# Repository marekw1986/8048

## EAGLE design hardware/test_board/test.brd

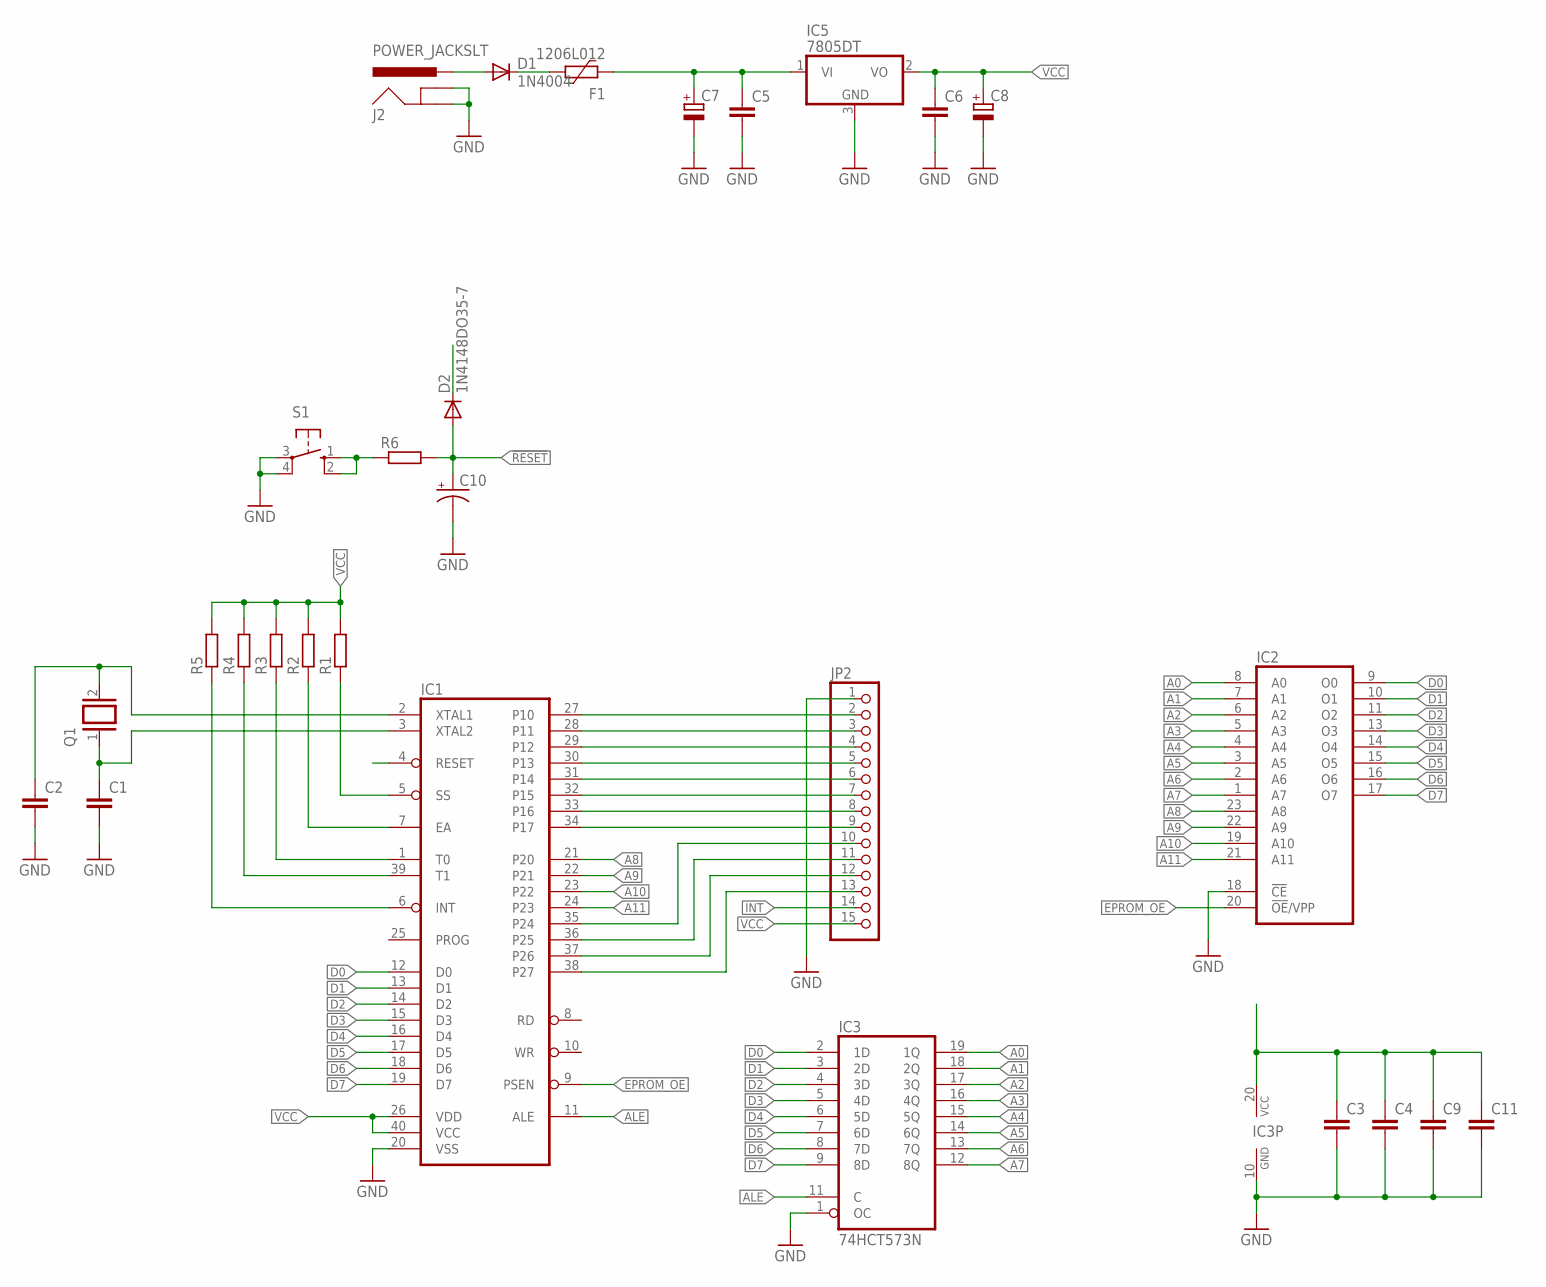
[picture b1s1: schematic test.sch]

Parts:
C1, C2, C3, C4, C5, C6, C9, C11: C-EUC0603; C0603
C7, C8: CPOL-EUSMCB; SMC_B
C10: CPOL-USE2,5-6E; E2,5-6E
D1: 1N4004; DO41-10
D2: 1N4148DO35-7; DO35-7
F1: 1206L012; 1206L
IC1: 8048; DIL40
IC2: 2732; DIL24
IC3: 74HCT573N; DIL20
IC5: 7805DT; TO252
J2: POWER_JACKSLT; POWER_JACK_SLOT
JP2: PINHD-1X15; 1X15
Q1: XTAL/S; QS
R1, R2, R3, R5: R-EU_R1206; R1206
R4, R6: R-EU_R0603; R0603
S1: 10-XX; B3F-10XX

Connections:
9V: C5.1, C7.+, F1.2, IC5.1 (VI)
!RESET: C10.+, D2.A, IC1.4 (RESET), R6.2
A0: IC2.8 (A0), IC3.19 (1Q)
A1: IC2.7 (A1), IC3.18 (2Q)
A2: IC2.6 (A2), IC3.17 (3Q)
A3: IC2.5 (A3), IC3.16 (4Q)
A4: IC2.4 (A4), IC3.15 (5Q)
A5: IC2.3 (A5), IC3.14 (6Q)
A6: IC2.2 (A6), IC3.13 (7Q)
A7: IC2.1 (A7), IC3.12 (8Q)
A8: IC1.21 (P20), IC2.23 (A8)
A9: IC1.22 (P21), IC2.22 (A9)
A10: IC1.23 (P22), IC2.19 (A10)
A11: IC1.24 (P23), IC2.21 (A11)
ALE: IC1.11 (ALE), IC3.11 (C)
D0: IC1.12 (D0), IC2.9 (O0), IC3.2 (1D)
D1: IC1.13 (D1), IC2.10 (O1), IC3.3 (2D)
D2: IC1.14 (D2), IC2.11 (O2), IC3.4 (3D)
D3: IC1.15 (D3), IC2.13 (O3), IC3.5 (4D)
D4: IC1.16 (D4), IC2.14 (O4), IC3.6 (5D)
D5: IC1.17 (D5), IC2.15 (O5), IC3.7 (6D)
D6: IC1.18 (D6), IC2.16 (O6), IC3.8 (7D)
D7: IC1.19 (D7), IC2.17 (O7), IC3.9 (8D)
EPROM_OE: IC1.9 (PSEN), IC2.20 (!OE!/VPP)
GND: C1.2, C2.2, C3.2, C4.2, C5.2, C6.2, C7.-, C8.-, C9.2, C10.-, C11.2, IC1.20 (VSS), IC2.12 (GND), IC2.18 (!CE), IC3.1 (OC), IC3.10 (GND), IC5.3 (GND), J2.GND@1 (GNDBREAK), J2.GND@2 (GND), JP2.1, S1.3, S1.4 (P1)
INT: IC1.6 (INT), JP2.14, R5.1
unnamed: C1.1, IC1.3 (XTAL2), Q1.1
unnamed: C2.1, IC1.2 (XTAL1), Q1.2
unnamed: IC1.5 (SS), R1.1
unnamed: IC1.7 (EA), R2.1
unnamed: IC1.1 (T0), R3.1
unnamed: IC1.39 (T1), R4.1
unnamed: R6.1, S1.1 (S), S1.2 (S1)
unnamed: IC1.27 (P10), JP2.2
unnamed: IC1.28 (P11), JP2.3
unnamed: IC1.29 (P12), JP2.4
unnamed: IC1.30 (P13), JP2.5
unnamed: IC1.31 (P14), JP2.6
unnamed: IC1.32 (P15), JP2.7
unnamed: IC1.33 (P16), JP2.8
unnamed: IC1.34 (P17), JP2.9
unnamed: IC1.35 (P24), JP2.10
unnamed: D1.A, J2.PWR
unnamed: IC1.36 (P25), JP2.11
unnamed: D1.C, F1.1
unnamed: IC1.37 (P26), JP2.12
unnamed: IC1.38 (P27), JP2.13
VCC: C3.1, C4.1, C6.1, C8.+, C9.1, C11.1, D2.C, IC1.26 (VDD), IC1.40 (VCC), IC2.24 (VCC), IC3.20 (VCC), IC5.2 (VO), JP2.15, R1.2, R2.2, R3.2, R4.2, R5.2

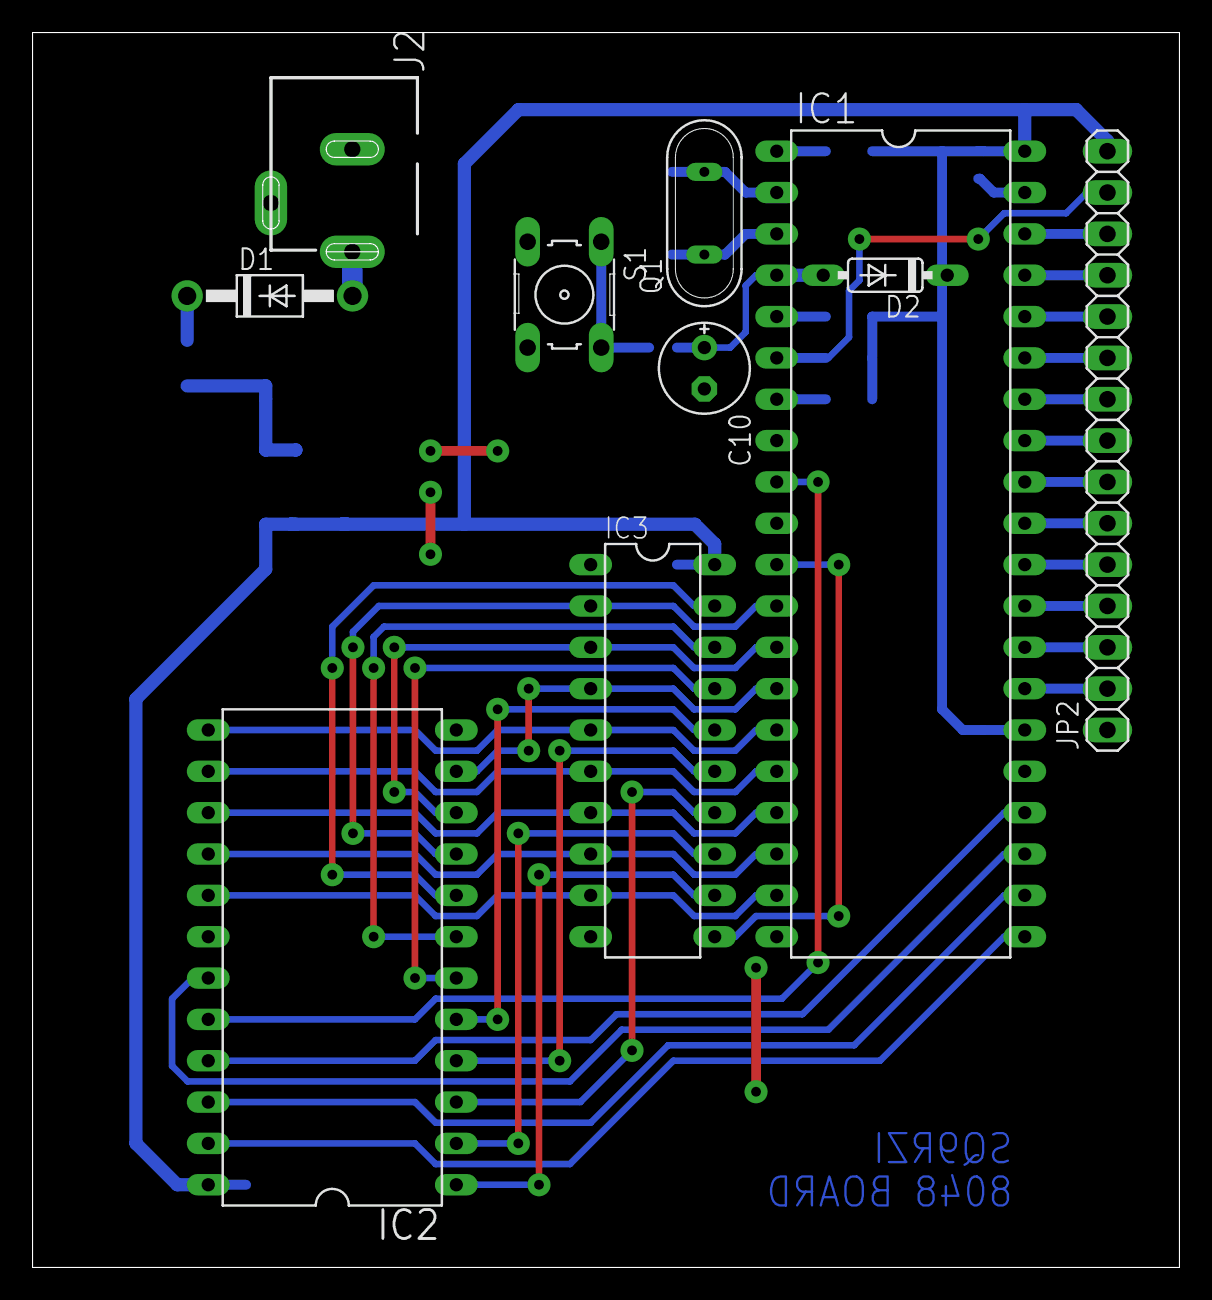
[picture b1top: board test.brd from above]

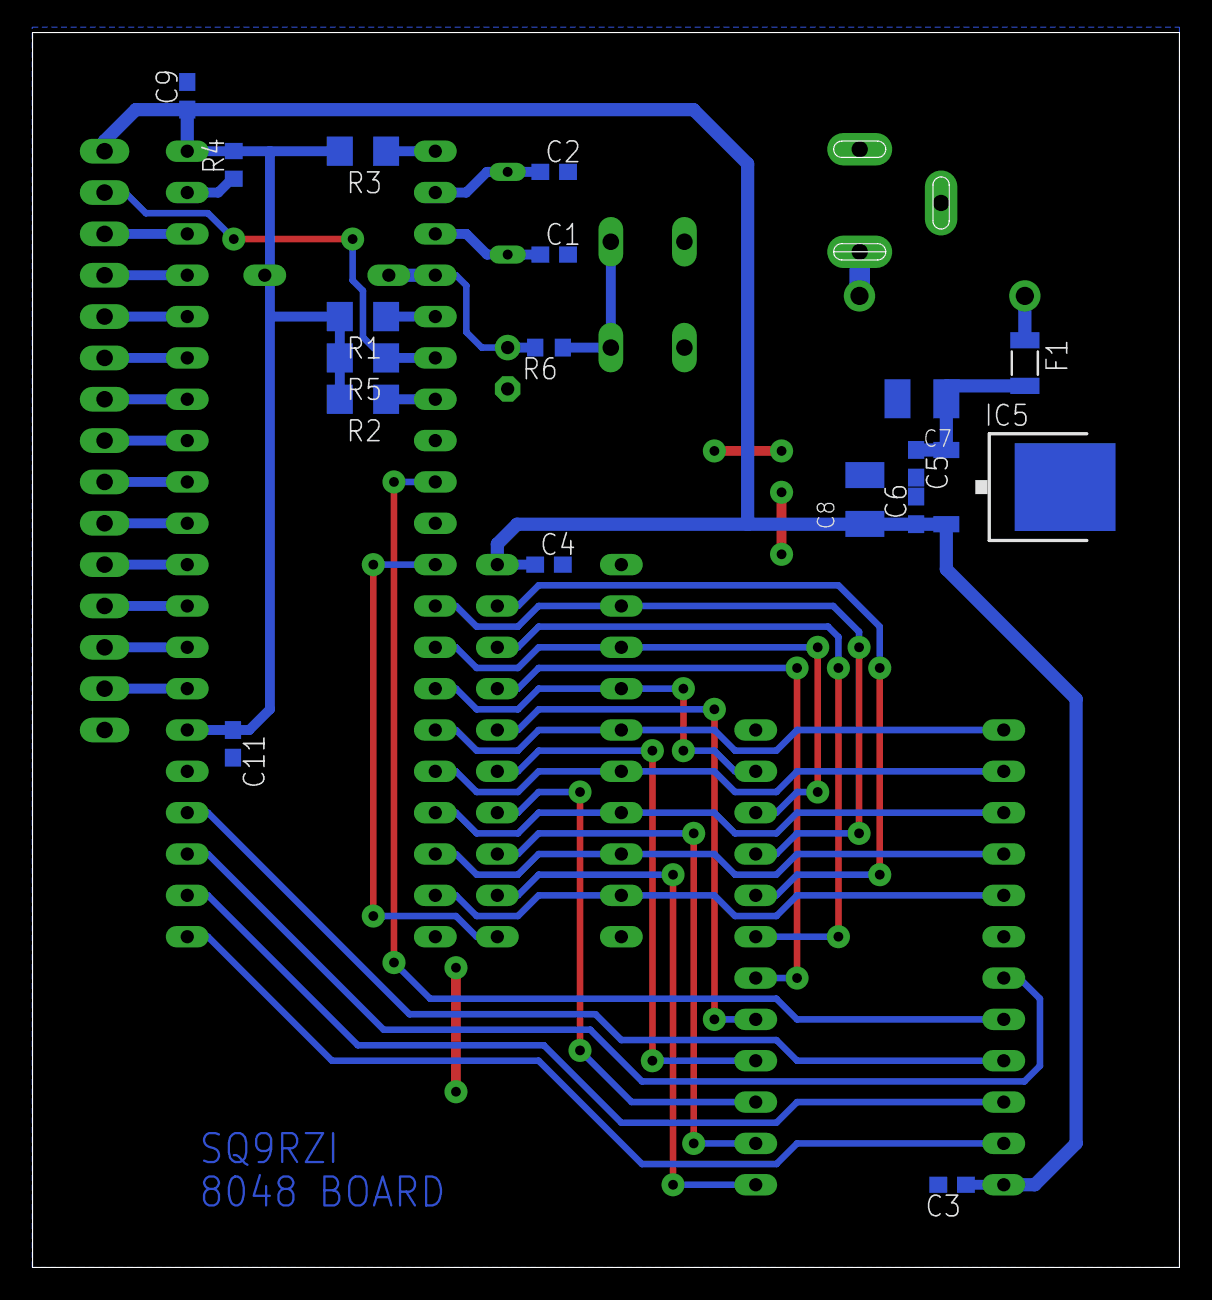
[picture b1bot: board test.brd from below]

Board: 2 copper layers, 70.5 x 75.9 mm, 28 parts (18 on the bottom side), 48 nets.

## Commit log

2024-07-17 RST circuit simplified according to datasheet
2024-07-17 Minor optimizations
2024-07-17 Few more optimizations
2024-07-20 Code examples and fix of bug in PCB design
2024-07-21 Code examples updated
2024-07-21 Prototype of procedure reading text
2024-07-21 Additional texts
2024-07-21 Blinking binary decoded ASCII
2024-07-21 Minor optimization
2024-07-22 CLK LED test
2024-07-22 CLK LED fix
2024-07-24 Diode aded at RST line
2024-07-26 Optimization. Using register instead of RAM
2024-07-27 Texts in separate files
2024-08-02 resetting cycle count after inpit change

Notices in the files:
parts and their libraries:
SparkFun-Connectors: Licensing: Creative Commons ShareAlike 4.0 International - https://creativecommons.org/licenses/by-sa/4.0
